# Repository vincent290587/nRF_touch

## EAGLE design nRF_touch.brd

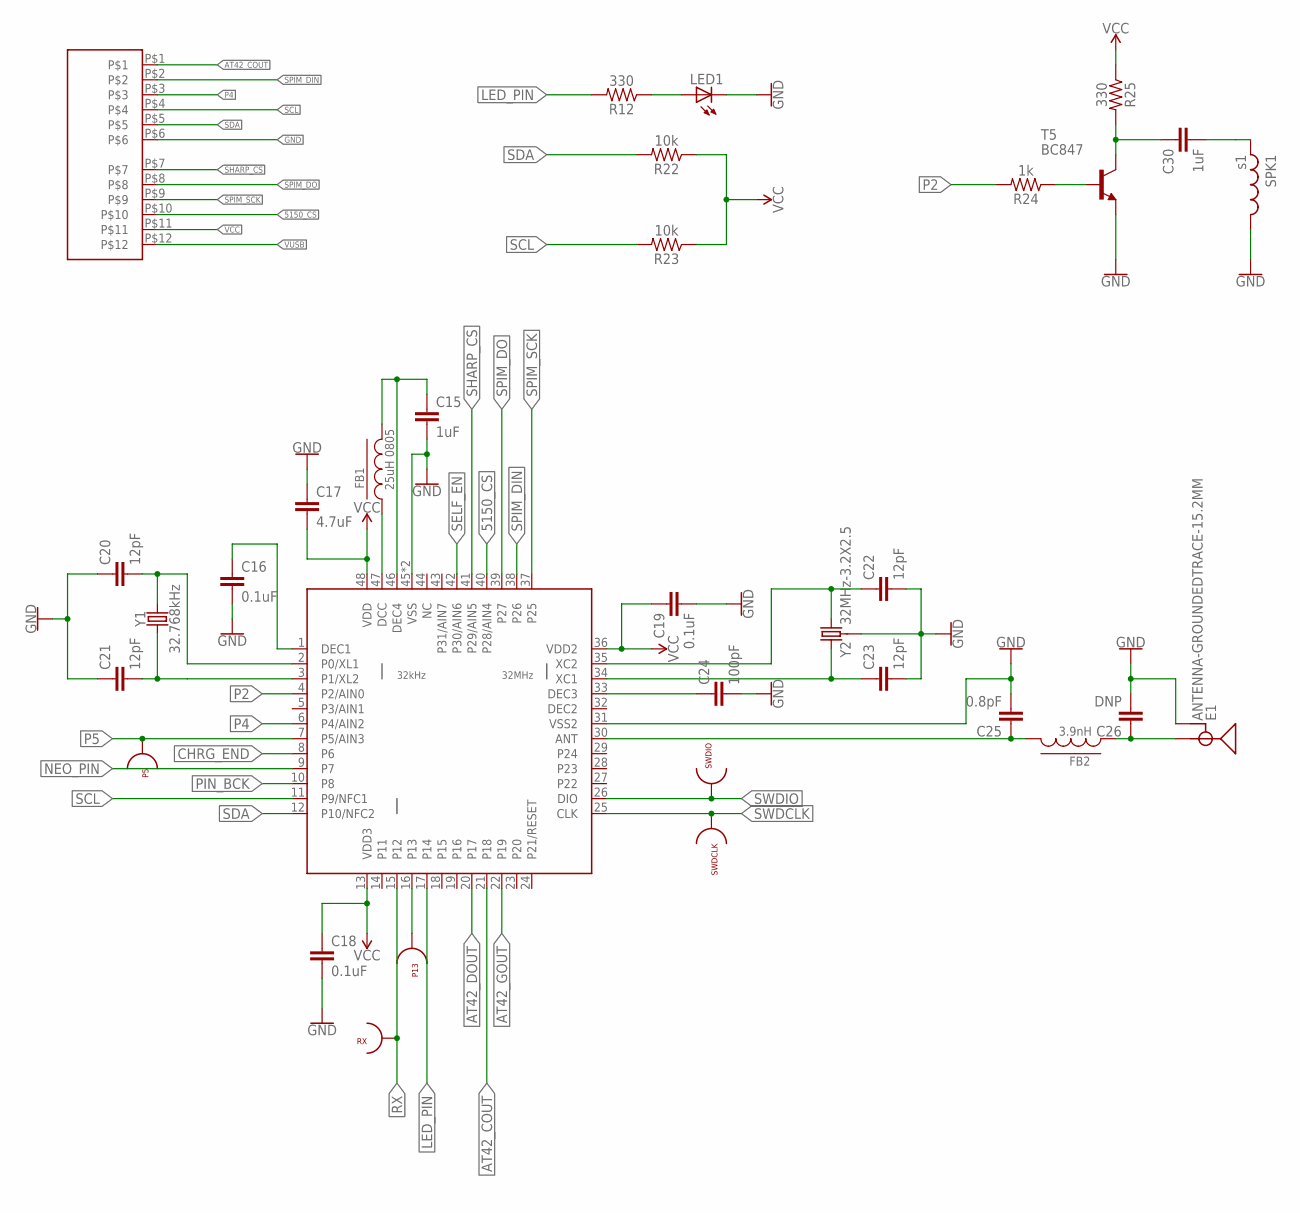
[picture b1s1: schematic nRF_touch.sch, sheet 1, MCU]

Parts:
C15, C30: 1uF; 0603
C16, C18, C19: 0.1uF; 0603
C17: 4.7uF; 0603
C20, C21, C22, C23: 12pF; 0603
C24: 100pF; 0603
C25: 0.8pF; 0603
C26: DNP; 0603
CONN2: 503480-1200
E1: ANTENNA-GROUNDEDTRACE-15.2MM; TRACE_ANTENNA_2.4GHZ_15.2MM
FB1: 25uH 0805; L0805
FB2: 3.9nH; L0805
LED1: LEDCHIPLED_1206; CHIPLED_1206
P5, P13: TESTPOINT_22
R12, R25: 330; 0603
R22, R23: 10k; 0603
R24: 1k; 0603
RX: TESTPOINT_22
SPK1: s1; IND-2020
SWDCLK: TESTPOINT_22
SWDIO: TESTPOINT_22
T5: BC847; SOT23
U$6: NRF52832NRF52832-QFAA; QFN48
Y1: 32.768kHz; CRYSTAL-SMD-3.2X1.5MM
Y2: 32MHz-3.2X2.5; CRYSTAL-SMD-5X3.2-4PAD

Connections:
5150_CS: CONN2.P$10, U$6.40 (P28/AIN4)
AT42_COUT: CONN2.P$1, U$6.21 (P18); also elsewhere on the board
AT42_DOUT: U$6.20 (P17); also elsewhere on the board
AT42_GOUT: U$6.22 (P19); also elsewhere on the board
CHRG_END: U$6.8 (P6); also elsewhere on the board
DEC3: C24.1, U$6.33 (DEC3)
GND: C15.2, C16.2, C17.1, C18.2, C19.2, C20.1, C21.1, C22.2, C23.2, C24.2, C25.2, C26.2, CONN2.P$6, E1.GND, LED1.C, SPK1.P$2 (2), T5.2 (E), U$6.31 (VSS2), U$6.45 (VSS), U$6.GND (VSS), Y2.2 (3), Y2.4 (3); also elsewhere on the board
LED_PIN: R12.2, U$6.17 (P14)
unnamed: LED1.A, R12.1
unnamed: C30.1, R25.2, T5.3 (C)
unnamed: C15.1, FB1.2, U$6.46 (DEC4)
unnamed: C25.1, FB2.2, U$6.30 (ANT)
unnamed: FB1.1, U$6.47 (DCC)
unnamed: C16.1, U$6.1 (DEC1)
unnamed: C26.1, E1.ANT (SIGNAL), FB2.1
unnamed: C20.2, U$6.2 (P0/XL1), Y1.P$2 (2)
unnamed: C21.2, U$6.3 (P1/XL2), Y1.P$1 (1)
unnamed: C22.1, U$6.35 (XC2), Y2.1 (2)
unnamed: C23.1, U$6.34 (XC1), Y2.3 (1)
unnamed: C30.2, SPK1.P$1 (1)
unnamed: R24.1, T5.1 (B)
NEO_PIN: U$6.9 (P7); also elsewhere on the board
P2: R24.2, U$6.4 (P2/AIN0)
P4: CONN2.P$3, U$6.6 (P4/AIN2)
P5: P5.P$1, U$6.7 (P5/AIN3)
P13: P13.P$1, U$6.16 (P13)
PIN_BCK: U$6.10 (P8); also elsewhere on the board
RX: RX.P$1, U$6.15 (P12)
SCL: CONN2.P$4, R23.2, U$6.11 (P9/NFC1); also elsewhere on the board
SDA: CONN2.P$5, R22.2, U$6.12 (P10/NFC2); also elsewhere on the board
SELF_EN: U$6.42 (P30/AIN6); also elsewhere on the board
SHARP_CS: CONN2.P$7, U$6.41 (P29/AIN5); also elsewhere on the board
SPIM_DIN: CONN2.P$2, U$6.38 (P26)
SPIM_DO: CONN2.P$8, U$6.39 (P27); also elsewhere on the board
SPIM_SCK: CONN2.P$9, U$6.37 (P25); also elsewhere on the board
SWDCLK: SWDCLK.P$1, U$6.25 (CLK)
SWDIO: SWDIO.P$1, U$6.26 (DIO)
VCC: C17.2, C18.1, C19.1, CONN2.P$11, R22.1, R23.1, R25.1, U$6.13 (VDD3), U$6.36 (VDD2), U$6.48 (VDD); also elsewhere on the board
VUSB: CONN2.P$12; also elsewhere on the board

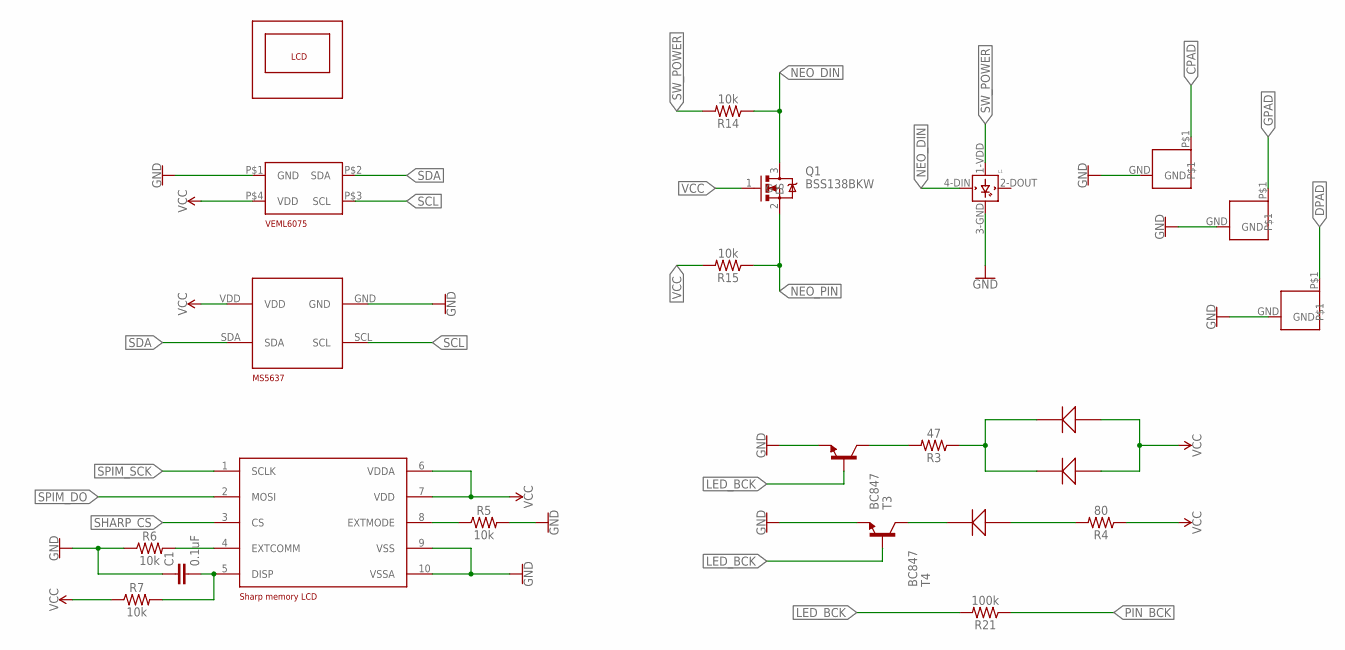
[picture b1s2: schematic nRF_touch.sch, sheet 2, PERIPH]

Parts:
C1: 0.1uF; 0603
L1: WS2812B
MS5637: MS5637
Q1: BSS138BKW; SOT65P210X110-3N
R3: 47; 0603
R4: 80; 0603
R5, R6, R7, R14, R15: 10k; 0603
R21: 100k; 0603
S1, S3: L_BUTTON; BUTTON
S2: BUTTON
T3, T4: BC847; SOT23
U$1, U$7, U$8: KPA-2106SECK
U$2: VEML6075
U$4: SHARP27
U$5: SHARP27_FOOTPRINT; LCD27

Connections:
CPAD: S2.P$1; also elsewhere on the board
DISP: C1.2, R7.2, U$4.5 (DISP)
DPAD: S1.P$1; also elsewhere on the board
EXTCOMM: R6.2, U$4.4 (EXTCOMM)
EXTMODE: R5.1, U$4.8 (EXTMODE)
GND: C1.1, L1.3-GND (GND), MS5637.GND, R5.2, R6.1, S1.GND, S2.GND, S3.GND, T3.2 (E), T4.2 (E), U$2.P$1 (GND), U$4.9 (VSS), U$4.10 (VSSA); also elsewhere on the board
GPAD: S3.P$1; also elsewhere on the board
LED_BCK: R21.2, T3.1 (B), T4.1 (B)
unnamed: R4.2, U$8.P$2
unnamed: R3.1, U$1.P$1, U$7.P$1
unnamed: T4.3 (C), U$8.P$1
unnamed: R3.2, T3.3 (C)
NEO_DIN: L1.4-DIN (DIN), Q1.3 (D), R14.1
NEO_PIN: Q1.2 (S), R15.1; also elsewhere on the board
PIN_BCK: R21.1; also elsewhere on the board
SCL: MS5637.SCL, U$2.P$3 (SCL); also elsewhere on the board
SDA: MS5637.SDA, U$2.P$2 (SDA); also elsewhere on the board
SHARP_CS: U$4.3 (CS); also elsewhere on the board
SPIM_DO: U$4.2 (MOSI); also elsewhere on the board
SPIM_SCK: U$4.1 (SCLK); also elsewhere on the board
SW_POWER: L1.1-VDD (VDD), R14.2; also elsewhere on the board
VCC: MS5637.VDD, Q1.1 (G), R4.1, R7.1, R15.2, U$1.P$2, U$2.P$4 (VDD), U$4.6 (VDDA), U$4.7 (VDD), U$7.P$2; also elsewhere on the board

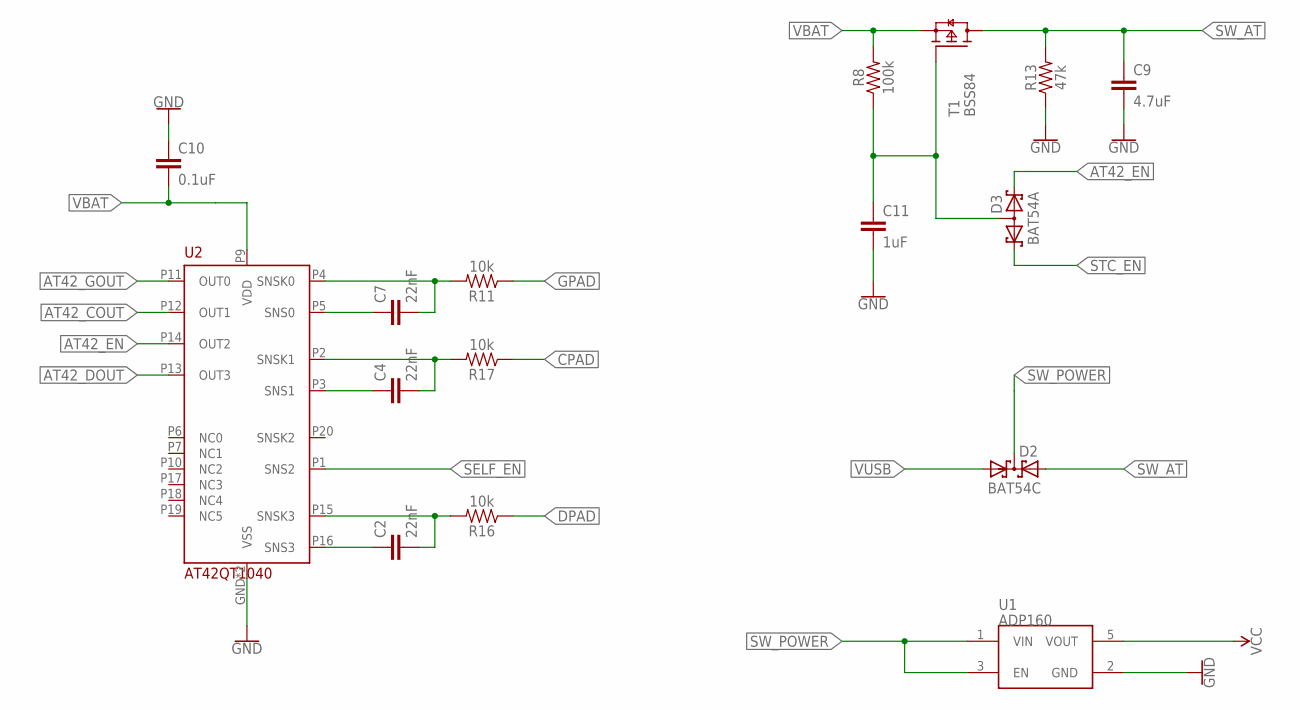
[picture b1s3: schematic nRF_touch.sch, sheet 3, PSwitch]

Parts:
C2, C4, C7: 22nF; 0603
C9: 4.7uF; 0603
C10: 0.1uF; 0603
C11: 1uF; 0603
D2: BAT54C; SOT23
D3: BAT54A; SOT23
R8: 100k; 0603
R11, R16, R17: 10k; 0603
R13: 47k; 0603
T1: BSS84; SOT23
U1: ADP160; SOT23-5
U2: AT42QT1040; VQFN20

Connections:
AT42_COUT: U2.P12 (OUT1); also elsewhere on the board
AT42_DOUT: U2.P13 (OUT3); also elsewhere on the board
AT42_EN: D3.2 (K2), U2.P14 (OUT2)
AT42_GOUT: U2.P11 (OUT0); also elsewhere on the board
CPAD: R17.1; also elsewhere on the board
DPAD: R16.1; also elsewhere on the board
GND: C9.2, C10.1, C11.2, R13.1, U1.2 (GND), U2.GND (VSS), U2.P8 (VSS); also elsewhere on the board
GPAD: R11.1; also elsewhere on the board
unnamed: C2.2, R16.2, U2.P15 (SNSK3)
unnamed: C2.1, U2.P16 (SNS3)
unnamed: C4.2, R17.2, U2.P2 (SNSK1)
unnamed: C7.2, R11.2, U2.P4 (SNSK0)
unnamed: C7.1, U2.P5 (SNS0)
unnamed: C11.1, D3.3 (A1A2), R8.1, T1.1 (G)
unnamed: C4.1, U2.P3 (SNS1)
SELF_EN: U2.P1 (SNS2); also elsewhere on the board
STC_EN: D3.1 (K1); also elsewhere on the board
SW_AT: C9.1, D2.2 (A2), R13.2, T1.3 (D)
SW_POWER: D2.3 (K1K2), U1.1 (VIN), U1.3 (EN); also elsewhere on the board
VBAT: C10.2, R8.2, T1.2 (S), U2.P9 (VDD); also elsewhere on the board
VCC: U1.5 (VOUT); also elsewhere on the board
VUSB: D2.1 (A1); also elsewhere on the board

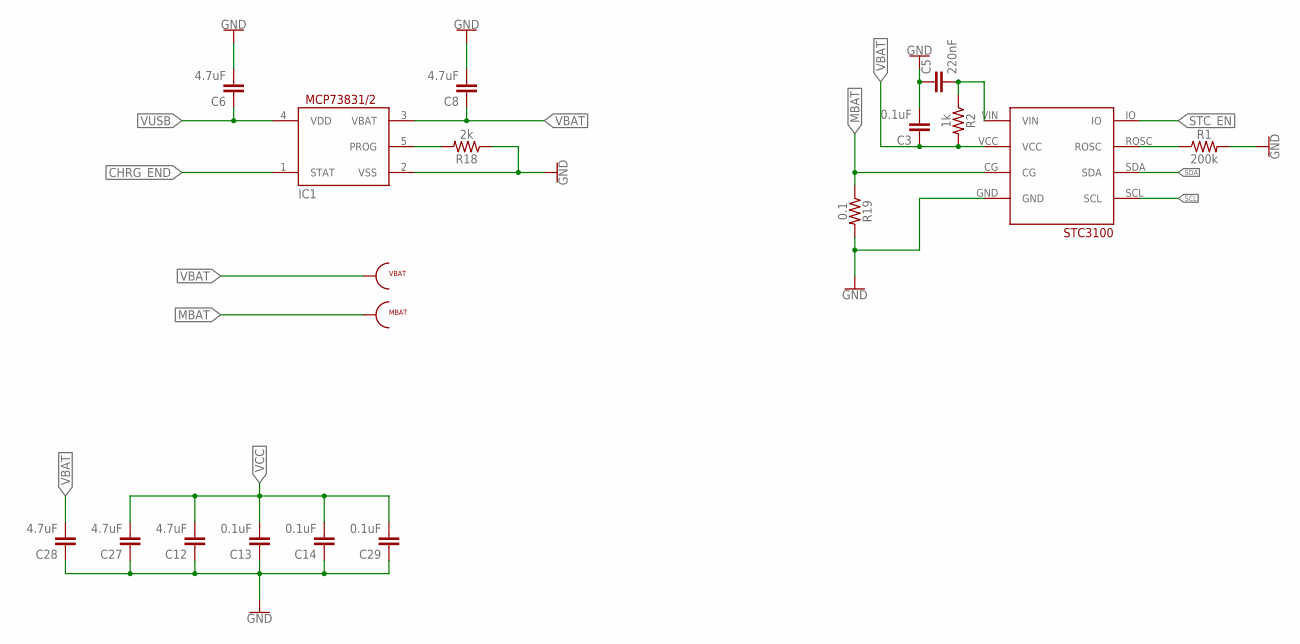
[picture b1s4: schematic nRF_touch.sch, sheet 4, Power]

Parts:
C3, C13, C14, C29: 0.1uF; 0603
C5: 220nF; 0603
C6, C8, C12, C27, C28: 4.7uF; 0603
IC1: MCP73831/OT; SOT23-5L
MBAT: TESTPOINT_22
R1: 200k; 0603
R2: 1k; 0603
R18: 2k; 0603
R19: 0.1; 0603
U$3: STC3100
VBAT: TESTPOINT_22

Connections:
CHRG_END: IC1.1 (STAT); also elsewhere on the board
GND: C3.2, C5.1, C6.2, C8.2, C12.1, C13.1, C14.1, C27.1, C28.1, C29.1, IC1.2 (VSS), R1.2, R18.1, R19.2, U$3.GND; also elsewhere on the board
MBAT: MBAT.P$1, R19.1, U$3.CG
unnamed: C5.2, R2.1, U$3.VIN
unnamed: IC1.5 (PROG), R18.2
unnamed: R1.1, U$3.ROSC
SCL: U$3.SCL; also elsewhere on the board
SDA: U$3.SDA; also elsewhere on the board
STC_EN: U$3.IO; also elsewhere on the board
VBAT: C3.1, C8.1, C28.2, IC1.3 (VBAT), R2.2, U$3.VCC, VBAT.P$1; also elsewhere on the board
VCC: C12.2, C13.2, C14.2, C27.2, C29.2; also elsewhere on the board
VUSB: C6.1, IC1.4 (VDD); also elsewhere on the board

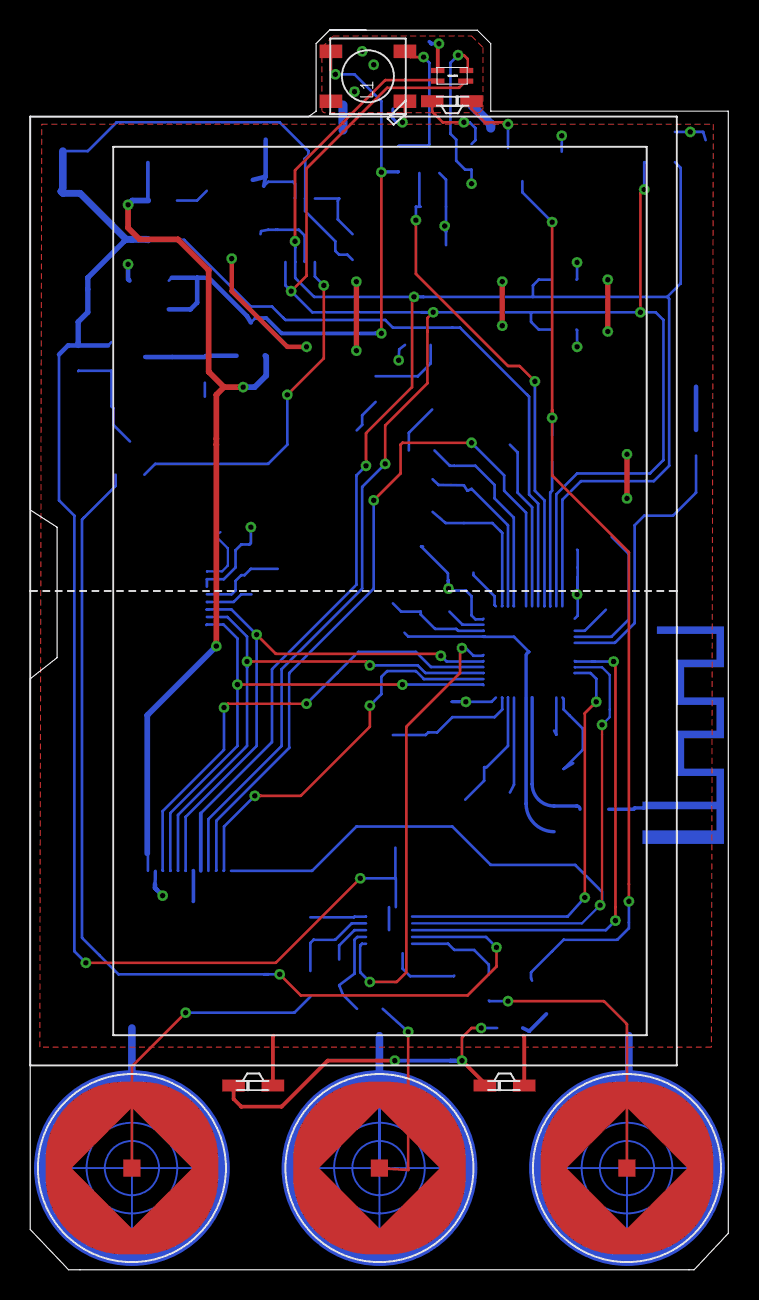
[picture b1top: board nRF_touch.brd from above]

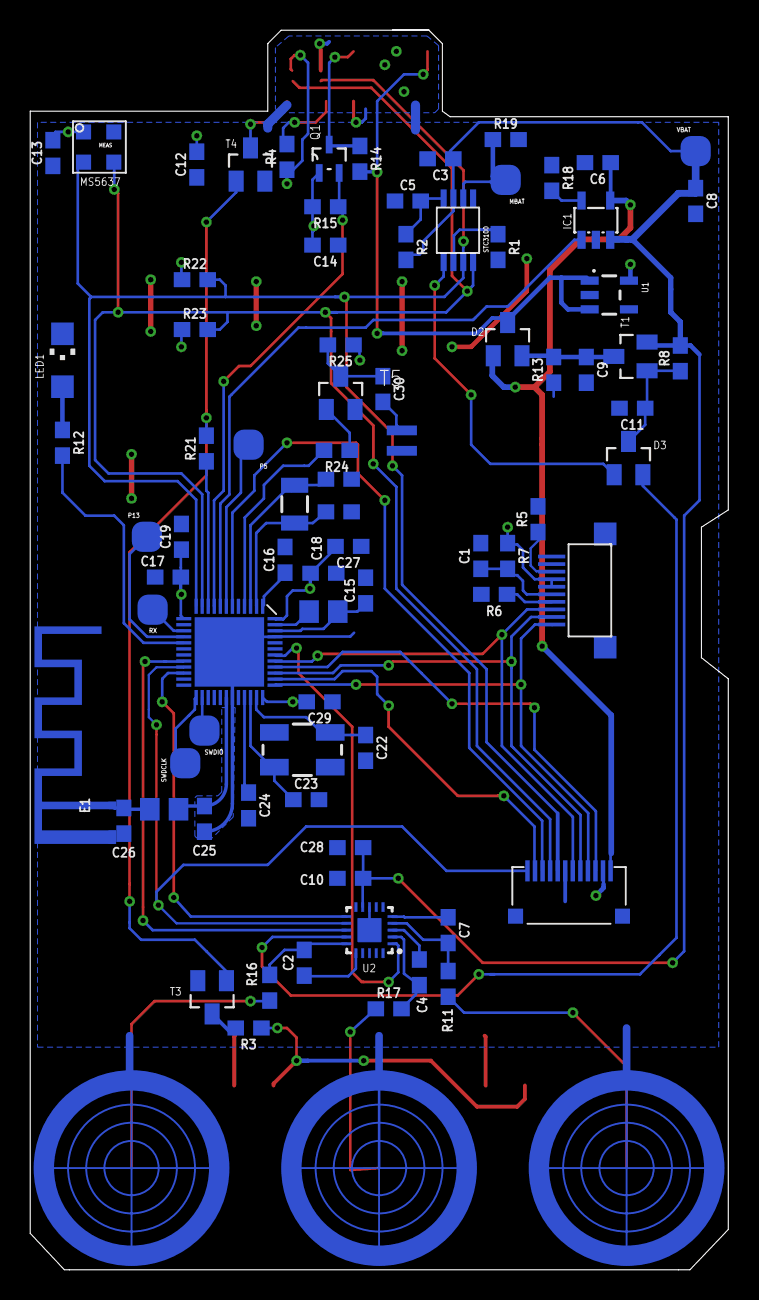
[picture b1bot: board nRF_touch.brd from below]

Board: 2 copper layers, 46.2 x 82.0 mm, 90 parts (81 on the bottom side), 67 nets.

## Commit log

2017-07-25 Placed components
2017-07-25 First routing
2017-07-25 Modified stop on qtouch
2017-07-25 Improvements #1
2017-07-26 Optimizations
2017-08-24 Addition of neopixel and change in logic
2017-09-14 Start placing components
2017-09-14 Finished placing
2017-09-14 First try at routing
2017-09-14 Routing complete
2017-09-14 Added resistors Routing optimized
2017-09-15 Errors corrected #1
2017-09-15 Smashing
2017-09-15 Screen hole
2017-09-15 Fusion
2017-10-21 -Same dimensions for top and bottom -more pads exposed -different power distribution
2017-10-21 Remodelled neopixel PCB part
2017-12-20 Routing done

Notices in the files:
parts and their libraries:
SparkFun-Resistors: Licensing: Creative Commons ShareAlike 4.0 International - https://creativecommons.org/licenses/by-sa/4.0
